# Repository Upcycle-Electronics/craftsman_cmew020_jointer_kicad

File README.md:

# craftsman_cmew020_jointer_kicad
KiCAD schematic and board files for the U2010B based universal AC motor speed control board

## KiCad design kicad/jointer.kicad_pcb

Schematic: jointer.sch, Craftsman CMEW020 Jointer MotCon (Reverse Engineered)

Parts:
C2: 100ηF; C_Rect_L11.0mm_W5.1mm_P10.00mm_MKT
C3: 10ηF; C_Rect_L4.6mm_W3.0mm_P2.50mm_MKS02_FKP02
C7: 150ηF; C_Disc_D7.0mm_W2.5mm_P5.00mm
CP1: 47μF; CP_Radial_D6.3mm_P2.50mm
CP2: 10μF; CP_Radial_D6.3mm_P2.50mm
CP3: 1μF; CP_Radial_D6.3mm_P2.50mm
D1: 1N4007; D_DO-41_SOD81_P10.16mm_Horizontal
D2: 1N4148; D_DO-35_SOD27_P10.16mm_Horizontal
IC1: U2010B; DIP-16_W7.62mm_LongPads
IC-ref1: U2010B; DIP-16_W7.62mm_LongPads
J1, J2: Jumper_NC_Small; SolderWire-0.5sqmm_1x02_P4.6mm_D0.9mm_OD2.1mm
M1: Motor
Q2: BTA26-600B; TO-3P-3_Vertical
R2: 150K; R_Axial_DIN0207_L6.3mm_D2.5mm_P10.16mm_Horizontal
R3, R7: 3k3; R_Axial_DIN0207_L6.3mm_D2.5mm_P10.16mm_Horizontal
R4: 47K; R_Axial_DIN0207_L6.3mm_D2.5mm_P10.16mm_Horizontal
R5, R9: 100R; R_Axial_DIN0207_L6.3mm_D2.5mm_P10.16mm_Horizontal
R6: 50K; Potentiometer_Vishay_T73YP_Vertical
R10: 4K7; R_Axial_DIN0207_L6.3mm_D2.5mm_P10.16mm_Horizontal
R11: 3K3; R_Axial_DIN0207_L6.3mm_D2.5mm_P10.16mm_Horizontal
R12: 100K; R_Axial_DIN0207_L6.3mm_D2.5mm_P10.16mm_Horizontal
R13: 5K; cmew020-pot
SW1: Red Panel Switch
T1: #1 Black; spade-terminal
T2: #2 White; spade-terminal
T3: #3 White; spade-terminal
WWR1: 0.1R; R_Axial_Power_L38.0mm_W9.0mm_P40.64mm
WWR2: 0.1R; R_Axial_Power_L38.0mm_W9.0mm_P45.72mm
WWR3: 8K2 / 5W; R_Axial_Power_L25.0mm_W9.0mm_P27.94mm

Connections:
Motor_Control: M1.2, Q2.2 (A2), R9.2, T2.1
unnamed: C2.1, R9.1
unnamed: C3.1, IC1.3 (Cφ)
unnamed: C7.1, CP2.2, IC1.6 (ILOAD), IC1.8 (VREF), J1.1
unnamed: C7.2, D2.2 (A), IC1.4 (CONTROL), IC1.5 (COMP), R10.2
unnamed: CP1.2, IC1.11 (VS), IC1.12 (HIGH_LOAD), R6.1, WWR3.1
unnamed: CP2.1, IC1.7 (CSOFT)
unnamed: CP3.2, J1.2, R13.1
unnamed: D1.2 (A), WWR3.2
unnamed: D2.1 (K), R12.2
unnamed: IC1.1 (ISENSE), R7.2
unnamed: IC1.2 (ISENSE), R3.1
unnamed: IC1.14 (VRφ), R4.1
unnamed: IC1.15 (VSYNC), R2.1
unnamed: IC1.16 (OUTPUT), R5.1
unnamed: J2.1, R10.1
unnamed: J2.2, R13.2
unnamed: Q2.1 (A1), R7.1, WWR1.2, WWR2.2
unnamed: Q2.3, R5.2
unnamed: R4.2, R6.2, R6.3
unnamed: R11.2, R13.3
Switch_LINE: D1.1 (K), M1.1, R2.2, SW1.2, T1.1
Switch_NEUTRAL: C2.2, C3.2, CP1.1, CP3.1, IC1.10 (GND), R3.2, R11.1, R12.1, SW1.4, T3.1, WWR1.1, WWR2.1

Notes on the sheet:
V,6(WWR1+WWR2)=+-250mV
Mode= B. Autostart
αmax
https://www.eevblog.com/forum/reviews/2021-craftsman-bench-jointer-cmew020-help-me-reverse-engineerhack-this-please/
CMEW020
NOTES: DC is rectified at D1 for a negative rail to power the U2010B. Ground is above this negative rail.
P11 MAX: Sink Current= 30mA Symb= -I,S t < 10μs= 100mA Symb= -i,s
P15 MAX: Synchronous Currents= 5mA Symb= +-I,syncV t < 10μs= 20mA Symb= +-i,syncV
P4,8 MAX: Phase Control >> Control Voltage= 0-V,8 Symb= -V,I P4 MAX: Phase Control >> Input Current= 500μA Symb= +-I,I
P14 MAX: Phase Control >> Charging Current= 0.5mA Symb= -I,jtmax
P7,8 Max: Soft Start >> Input Voltage= 0-V8 Symb= -V,I
P16 MAX: Pulse Output >> Input Voltage: Symb= +V,I == 2 volts Symb= -V,I == V,11
P8 MAX: Reference Voltage Source >> Output Current= 10mA // t < 10μs= 30mA Symb= I,O
P1,2 MAX: Load-Current Sensing >> Input Currents= 1mA Symb= +-I,i
P5,6 MAX: Load-Current Sensing >> Input Voltages= 0 - V,8 Symb= -V,i
P13 MAX: Load-Current Sensing >> Overload Output= 1mA Symb= I,L
P12 MAX: Load-Current Sensing >> High-Load Output= 30mA t < 10μs = 100mA Symb= I,L
mains syncronized

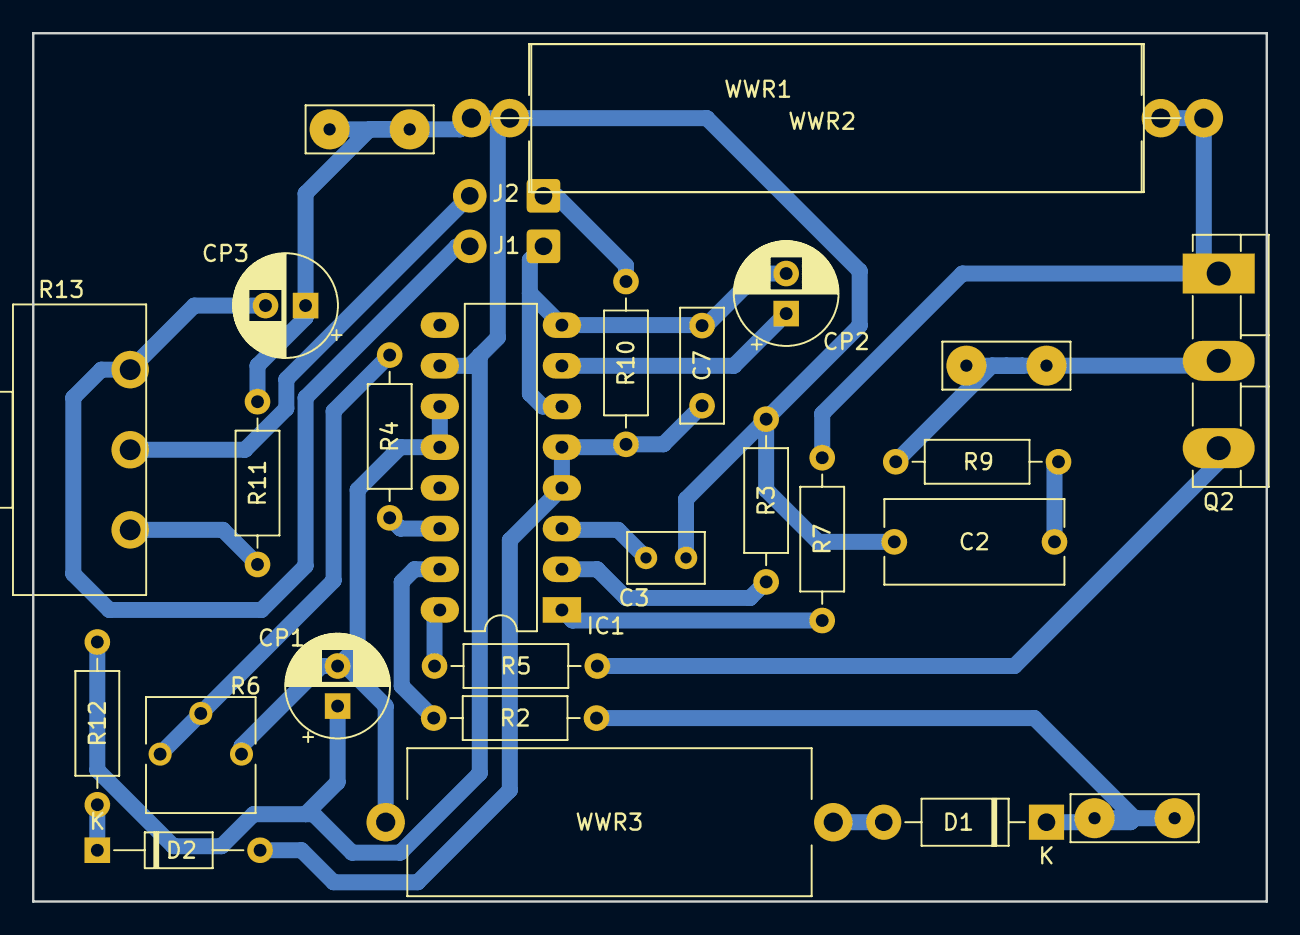
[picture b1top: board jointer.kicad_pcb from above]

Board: 2 copper layers, 77.0 x 54.2 mm, 29 parts (0 on the bottom side), 23 nets.

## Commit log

2021-03-21 Version 1.1

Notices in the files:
kicad/jointer.sch:
Copyright Jake Little 2021
MIT License
